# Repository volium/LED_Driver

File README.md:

# LED_Driver
LED Driver based on boost IC

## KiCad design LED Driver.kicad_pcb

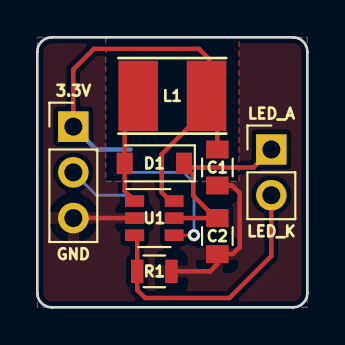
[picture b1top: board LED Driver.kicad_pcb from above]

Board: 2 copper layers, 15.0 x 15.0 mm, 9 parts (0 on the bottom side), 7 nets.

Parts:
C1, C2: 1uF; C_0805
D1: MBR0530; D_SOD-123
J1: CONN_01X02; Pin_Header_Straight_1x02_Pitch2.54mm
J2: CONN_01X03; Pin_Header_Straight_1x03_Pitch2.54mm
J3: GS3
L1: 22uH; Inductor_Taiyo-Yuden_NR-40xx_HandSoldering
R1: 2.55; R_0805
U1: AP5724; SOT-23-6

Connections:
+3V3: C1.1, J2.1, J3.1, L1.1, U1.6
/EN: J3.2, U1.4
/EN_CONN: J2.2, J3.3
/LED_A: C2.1, D1.1, J1.1, U1.5
/LED_K: J1.2, R1.1, U1.3
/SW: D1.2, L1.2, U1.1
GND: C1.2, C2.2, J2.3, R1.2, U1.2

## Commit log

2017-07-24 First commit
    Adds initial schematic and pcb layout based on AP5724
2017-07-24 Moves D1 references out of PCB area
2017-07-24 Reworked layout to bring C1 closer to VCC input of AP5724
2017-07-25 Finished updated layout
    Moved things around to place C1 and C2 on right side of AP5724
    Shrinked board to 15 x 15 mm
    Adds solder bridge for EN pin (VCC or EN pin)
2017-07-25 Replaces AP5824 with NCP5006, removed unnecessary OV track, minor cleanup
2017-07-25 Adds explicit VOUT net, moves it "Power" class
    Removed unnecessary tracks, overall cleanup
2017-07-25 Adds explicit "SW" net, and made it "Power" class Replaced SDM20U40 diode with MBR0530 (kept D_SOD-123 package) Cleanup of tracks
2017-07-26 Cleanup
    Moved components, copper pours and via to properly align
    Changed copper pour parameters
2017-07-26 Renamed Top and Bottom layers Removed unused layers
2017-07-26 Fixed copper pour alignment
2017-07-26 Recalculater copper pours
2017-07-26 Updated copper pour paramters and recalculated top and bottom masks
2017-07-26 Fixed alignment of R1, redid some tracks
2017-07-26 Recalculated copper pours
2017-07-26 Added labels and component references to Silkscreen
2017-07-26 Moved component references back in to place (changed size)
2017-07-26 Adds labels to silkscreen (copied from NCP5006 branch)
2017-07-27 Adds project name and version (v1.0) to silkscreen
2017-07-27 Adds gerber files
2017-07-27 Updates pcb file after plotting gerber files
2017-07-27 Adds gerber files, updates pcb file
2017-07-30 Updates 3D Model for L1
    Updated 3D Model for L1 (Inductor_Taiyo-Yuden_NR-40xx_HandSoldering) to use new NR4018 in 3DModels repository
2017-07-31 Updates 3D Models
    Updates 3D model for D1, LED MBR0530 to use new SOD123 model in 3DModels repository
    Updates 3D model for U1 NCP5006, TSOT-23-5 to use regular SOT-23-5 model
2017-07-31 Updates 3D Model
    Updates 3D model for D1, LED MBR0530 to use new SOD123 model in 3DModels repository
2017-08-13 Updates project after downloading new 3D models from github repository
    I followed instructions in this post:
    https://forum.kicad.info/t/update-the-libraries-modules-packages3d-from-github/5171/6
    to download new versions of all 3D models from github
    Removed rotations and shift offset from Pin Headers 3D models
    Replaced 3Model for D1 with Kicad's version of D_SOD-123.wrl
